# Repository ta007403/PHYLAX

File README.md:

# PHYLAX — Open-Source Bitcoin Hardware Wallet

**PHX-001 · Version 3 · Square Button**

PHYLAX (Greek *φύλαξ*, "guardian") is an open-source, Bitcoin-only hardware wallet built around a simple idea: no black-box chips, no wireless radios, no telemetry, and firmware you can read and verify yourself. This repository contains the KiCad hardware design files for the PHYLAX Version 3 board (square button variant).

🌐 Website: [phylaxwallet.com](https://phylaxwallet.com/)

> **Status:** In development — prototype targeted for Q4 2026. Hardware and firmware are subject to change.

---

## Why PHYLAX

- **Zero black-box chips** — no proprietary secure element; every component is one you can trace and verify.
- **Fully open firmware** — released under GPL v3.
- **Bitcoin-only** — no altcoins, no unnecessary attack surface.
- **No wireless radios, no telemetry** — the device only talks over USB-C, and only when you plug it in.
- **Built by the community** — the project is developed and audited in the open.

## What's in This Repository

This is a **KiCad 8 project** containing the schematic, PCB layout, 3D models, fabrication outputs, and supporting library parts for the PHYLAX board.

```
Phylax_Version_3 Square Button/
├── Phylax_Version_3.kicad_pro       # KiCad project file
├── Phylax_Version_3.kicad_sch       # Schematic
├── Phylax_Version_3.kicad_pcb       # PCB layout
├── 3D/                              # 3D models & case designs (.step, .stl, .FCStd, .scad)
├── Library/                         # Custom symbol, footprint, and 3D model libraries per part
├── Gerber/                          # Fabrication (Gerber/drill) outputs
├── PCB Outline/                     # Board outline drawings (DXF/PDF)
├── production/                      # BOM, position files, netlist, and production archives
├── Phylax_Version_3-backups/        # KiCad autosave/backup archives
├── fp-lib-table / sym-lib-table     # KiCad footprint & symbol library tables
└── Button Note.txt                  # Working design notes on component substitutions
```

### Key components

| Part | Role |
|---|---|
| STM32F205RET6 | Main microcontroller |
| SX1308 | Boost converter |
| MCP1703AT-3302E | 3.3V LDO regulator |
| USB4215-03-A | USB-C connector |
| SKHCBEA010 | Tactile push button |
| ABMM2-8.000MHZ-E2-T | Crystal oscillator |

*(See `production/bom.csv` for the full bill of materials.)*

## Getting Started

### Prerequisites

- [KiCad 8](https://www.kicad.org/download/) or later
- (Optional) [FreeCAD](https://www.freecad.org/) to view/edit the `.FCStd` case files
- (Optional) [OpenSCAD](https://openscad.org/) to view/edit the `.scad` case files

### Opening the project

1. Clone this repository:
   ```bash
   git clone https://github.com/ta007403/PHYLAX.git
   cd PHYLAX
   ```
2. Open `Phylax_Version_3.kicad_pro` in KiCad.
3. Schematic, PCB, and 3D viewer are all accessible from the KiCad project manager.

### Manufacturing

Fabrication-ready outputs (Gerbers, drill files, BOM, and pick-and-place data) are provided in the `Gerber/` and `production/` folders for sending directly to a PCB manufacturer/assembler.

## Contributing

PHYLAX is built in the open and welcomes community review and contributions — from schematic review to case design. Please open an issue or pull request with proposed changes. If you spot a design or safety issue, responsible disclosure is appreciated.

## License

Firmware and hardware design files are released under **GPL v3** unless otherwise noted. See the [PHYLAX manifesto](https://phylaxwallet.com/manifesto) and [specs](https://phylaxwallet.com/specs) for more on the project's philosophy and technical details.

## Links

- Website: [phylaxwallet.com](https://phylaxwallet.com/)
- Specifications: [phylaxwallet.com/specs](https://phylaxwallet.com/specs)
- Manifesto: [phylaxwallet.com/manifesto](https://phylaxwallet.com/manifesto)
- Journal / build updates: [phylaxwallet.com/journal](https://phylaxwallet.com/journal/)
- Facebook: [facebook.com/phylaxwallet](https://www.facebook.com/phylaxwallet)

---

*Not your keys, not your coins — PHYLAX gives you the keys.*

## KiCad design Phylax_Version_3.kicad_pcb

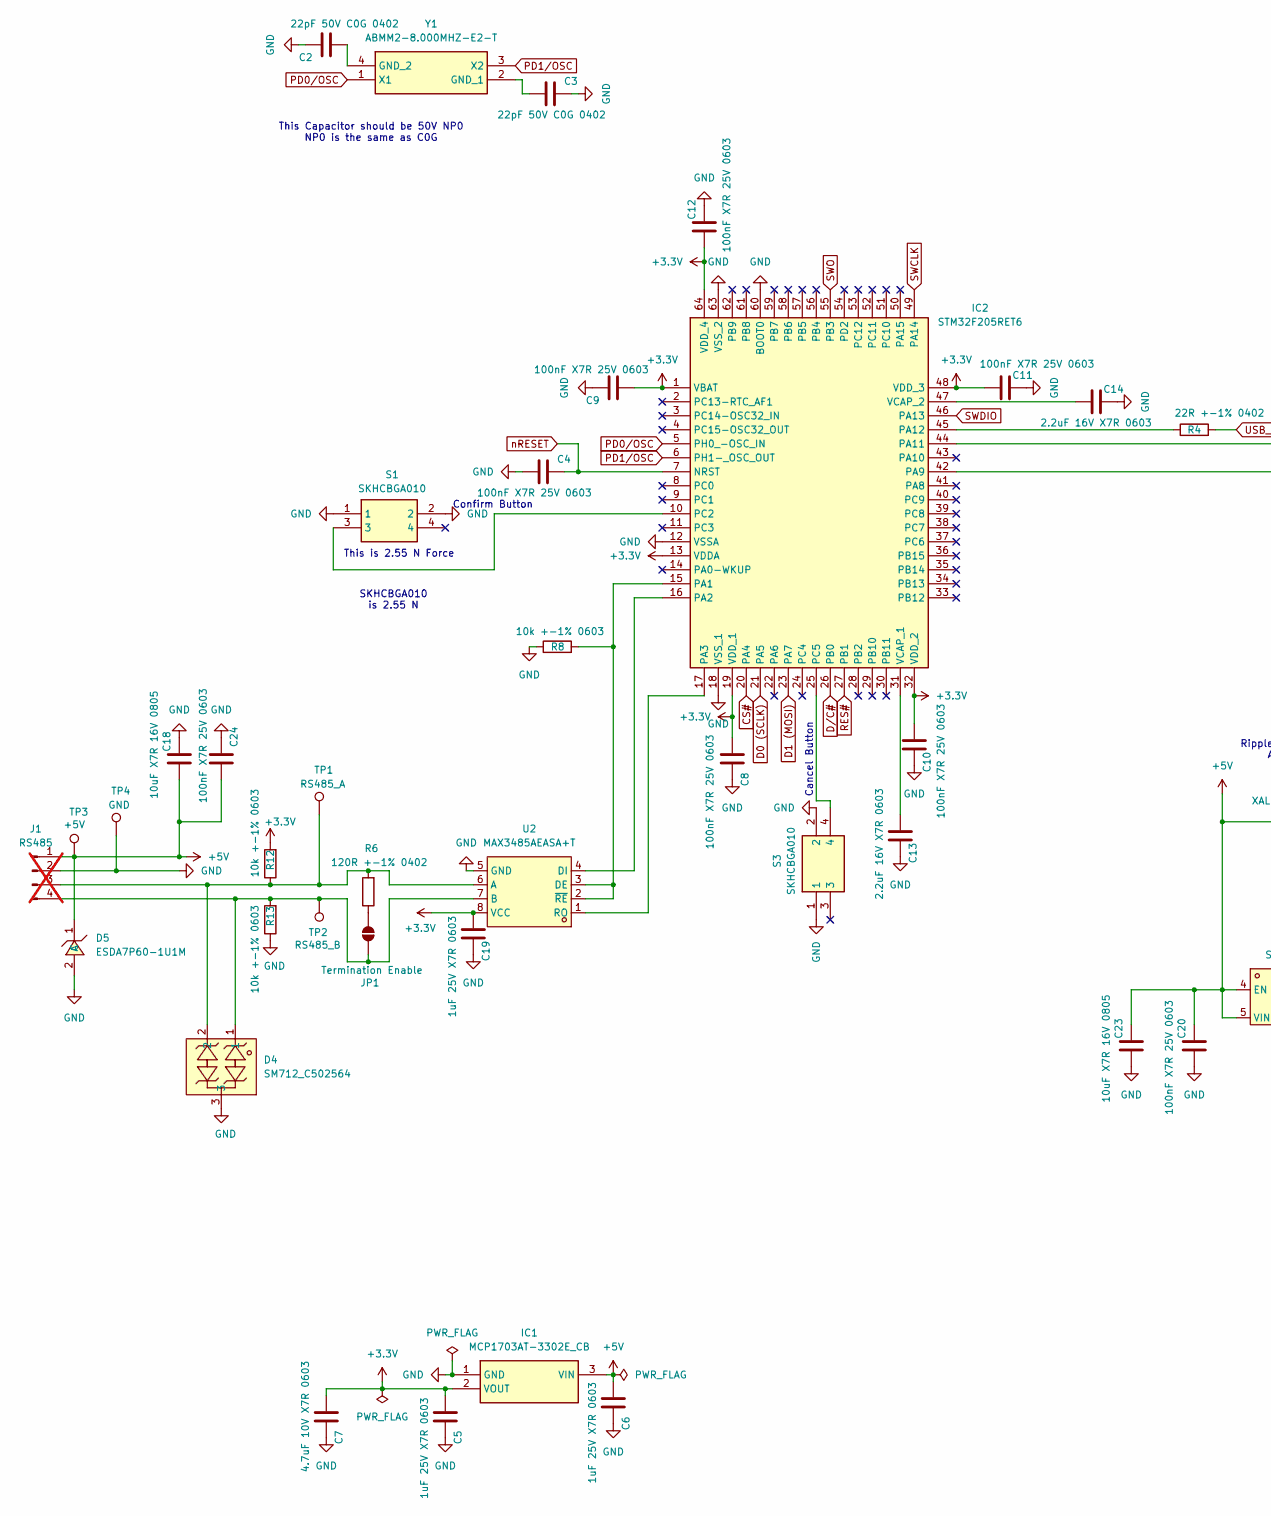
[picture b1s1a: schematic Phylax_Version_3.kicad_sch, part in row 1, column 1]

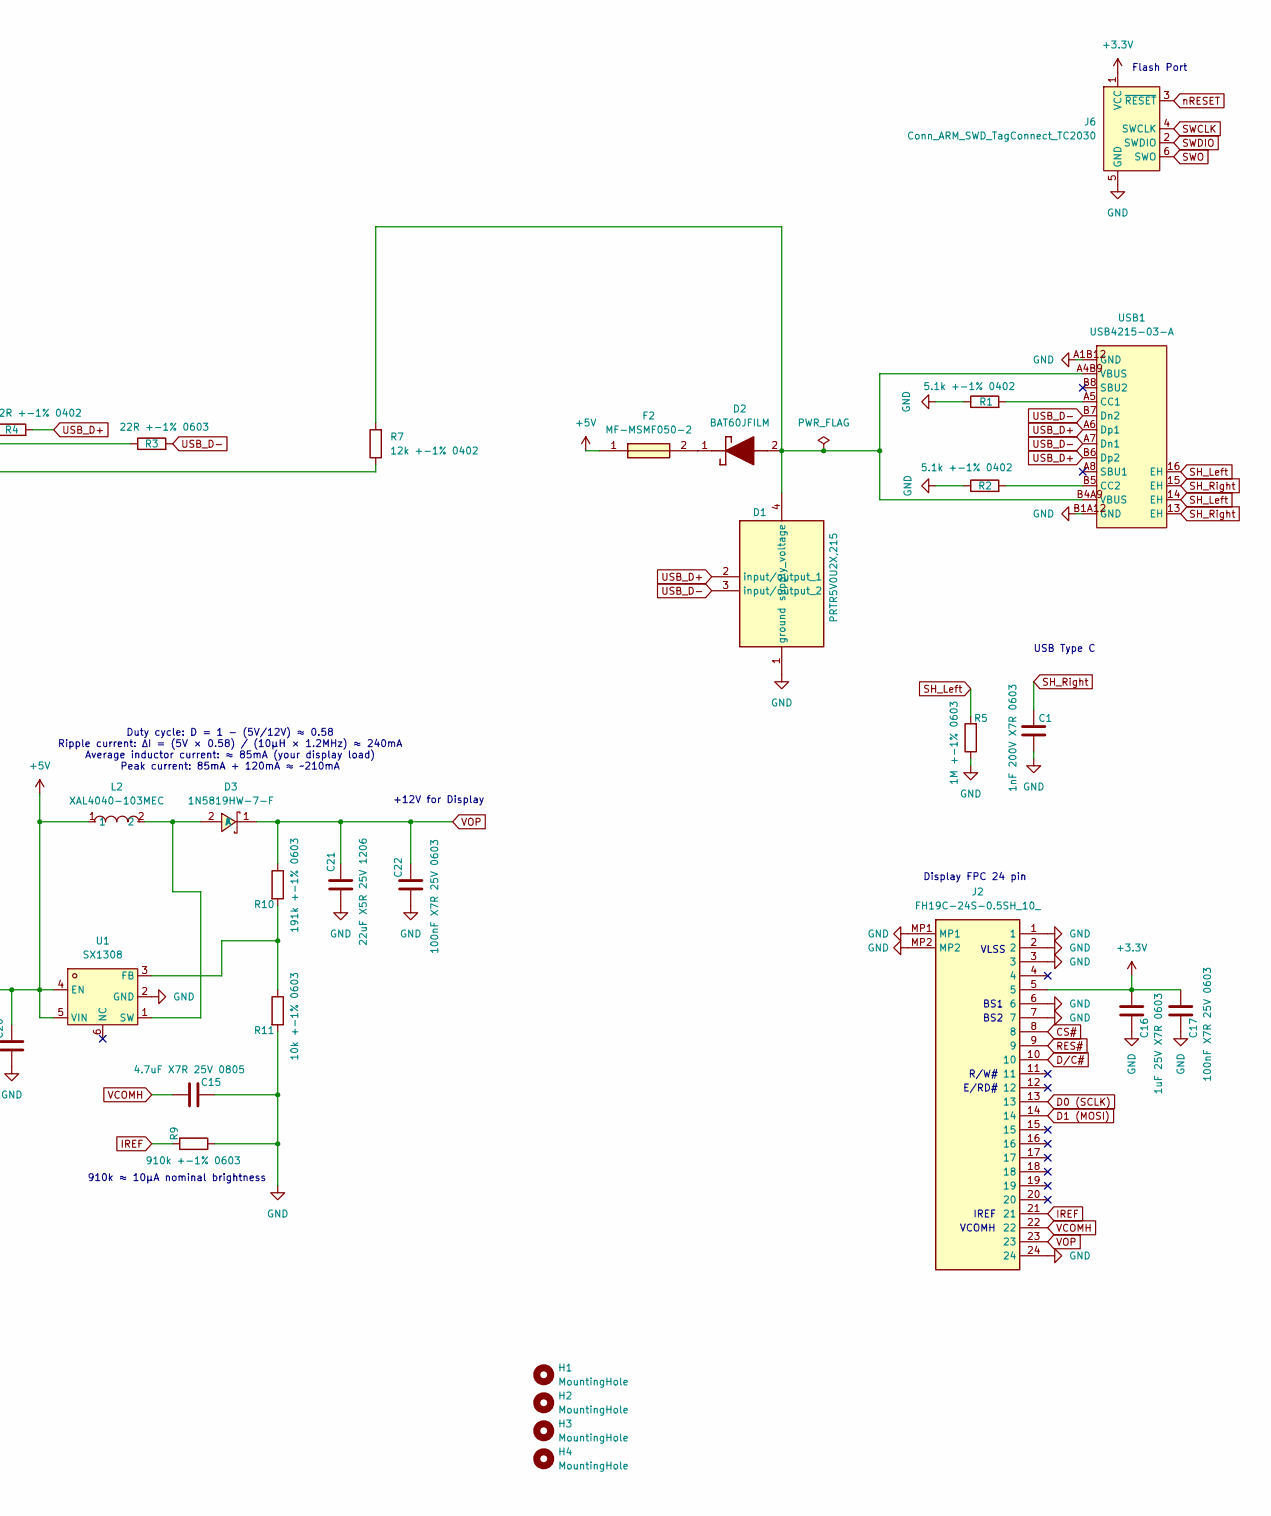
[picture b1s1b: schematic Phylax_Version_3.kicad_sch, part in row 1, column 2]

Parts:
C1: 1nF 200V X7R 0603; C_0603_1608Metric_Pad1.08x0.95mm_HandSolder; LCSC Part # C282243
C2, C3: 22pF 50V C0G 0402; C_0402_1005Metric_Pad0.74x0.62mm_HandSolder; LCSC Part # C106203
C4, C8, C9, C10, C11, C12, C17, C20, C22, C24: 100nF X7R 25V 0603; C_0603_1608Metric_Pad1.08x0.95mm_HandSolder; LCSC Part # C14663
C5, C6, C16, C19: 1uF 25V X7R 0603; C_0603_1608Metric_Pad1.08x0.95mm_HandSolder; LCSC Part # C106858
C7: 4.7uF 10V X7R 0603; C_0603_1608Metric_Pad1.08x0.95mm_HandSolder; LCSC Part # C18185770
C13, C14: 2.2uF 16V X7R 0603; C_0603_1608Metric_Pad1.08x0.95mm_HandSolder; LCSC Part # C914769
C15: 4.7uF X7R 25V 0805; C_0805_2012Metric_Pad1.18x1.45mm_HandSolder; LCSC Part # C354262
C18, C23: 10uF X7R 16V 0805; C_0805_2012Metric_Pad1.18x1.45mm_HandSolder; LCSC Part # C326595
C21: 22uF X5R 25V 1206; C_1206_3216Metric_Pad1.33x1.80mm_HandSolder; LCSC Part # C2178233
D1: PRTR5V0U2X,215; PRTR5V0U2X; Mouser Part Number 771-PRTR5V0U2X-T/R
D2: BAT60JFILM; SOD2513X117N; Mouser Part Number 511-BAT60JFILM
D3: 1N5819HW-7-F; SOD-123_L2.7-W1.6-LS3.7-RD; MPN 1N5819HW-7-F; LCSC Part C82544
D4: SM712_C502564; SOT-23-3_L2.9-W1.6-P1.90-LS2.8-BR; MPN SM712; LCSC Part C502564
D5: ESDA7P60-1U1M; D1610-RD; MPN ESDA7P60-1U1M; LCSC Part C1975146
F2: MF-MSMF050-2; FUSC4632X85N; Mouser Part Number 652-MF-MSMF050-2
H1, H2, H3, H4: MountingHole; MountingHole_3.2mm_M3
IC1: MCP1703AT-3302E_CB; SOT95P255X145-3N; Mouser Part Number 579-MCP1703AT3302ECB
IC2: STM32F205RET6; QFP50P1200X1200X160-64N; Mouser Part Number 511-STM32F205RET6
J1: RS485; PinHeader_1x04_P2.54mm_Vertical; not fitted
J2: FH19C-24S-0.5SH_10_; FH19C24S05SH10; Mouser Part Number 798-FH19C24S05SH10
J6: Conn_ARM_SWD_TagConnect_TC2030; Tag-Connect_TC2030-IDC-FP_2x03_P1.27mm_Vertical
JP1: Termination Enable; SolderJumper-2_P1.3mm_Open_RoundedPad1.0x1.5mm
L2: XAL4040-103MEC; IND-SMD_L4.0-W4.0_XAL4040; MPN XAL4040-103MEC; LCSC Part C5144883
R1, R2: 5.1k +-1% 0402; R_0402_1005Metric_Pad0.72x0.64mm_HandSolder; LCSC Part # C852856
R3: 22R +-1% 0603; R_0603_1608Metric_Pad0.98x0.95mm_HandSolder; LCSC Part # C313710
R4: 22R +-1% 0402; R_0402_1005Metric_Pad0.72x0.64mm_HandSolder; LCSC Part # C2686485
R5: 1M +-1% 0603; R_0603_1608Metric_Pad0.98x0.95mm_HandSolder; LCSC Part # C22356470
R6: 120R +-1% 0402; R_0603_1608Metric_Pad0.98x0.95mm_HandSolder; LCSC Part # C22787
R7: 12k +-1% 0402; R_0402_1005Metric_Pad0.72x0.64mm_HandSolder; LCSC Part # C2909316
R8, R11, R12, R13: 10k +-1% 0603; R_0603_1608Metric_Pad0.98x0.95mm_HandSolder; LCSC Part # C98220
R9: 910k +-1% 0603; R_0603_1608Metric_Pad0.98x0.95mm_HandSolder; LCSC Part # C23263
R10: 191k +-1% 0603; R_0603_1608Metric_Pad0.98x0.95mm_HandSolder; LCSC Part # C2974031
S1, S3: SKHCBGA010; Mouser Part Number 688-SKHCBGA010
TP1: RS485_A; TestPoint_Pad_1.0x1.0mm
TP2: RS485_B; TestPoint_Pad_1.0x1.0mm
TP3: +5V; TestPoint_Pad_1.0x1.0mm
TP4: GND; TestPoint_Pad_1.0x1.0mm
U1: SX1308; SOT-23-6_L2.9-W1.6-P0.95-LS2.8-BL; MPN SX1308; LCSC Part C78162
U2: MAX3485AEASA+T; SO-8_L4.9-W3.9-P1.27-LS5.9-BL; MPN MAX3485AEASA+T; LCSC Part C94609
USB1: USB4215-03-A; USB-C-SMD_GT-USB-7010B; MPN USB4215-03-A; LCSC Part C37616412
Y1: ABMM2-8.000MHZ-E2-T; ABMM2; Mouser Part Number 815-ABMM2-8-E2T

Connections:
+3.3V: C5.2, C7.2, C8.2, C9.2, C10.2, C11.2, C12.2, C16.2, C17.2, C19.2, IC1.2 (VOUT), IC2.1 (VBAT), IC2.13 (VDDA), IC2.19 (VDD_1), IC2.32 (VDD_2), IC2.48 (VDD_3), IC2.64 (VDD_4), J2.5, J6.1 (VCC), R12.2, U2.8 (VCC)
+5V: C6.2, C18.2, C20.1, C23.1, C24.1, D5.1 (C), F2.1, IC1.3 (VIN), J1.1, L2.1, TP3.1, U1.4 (EN), U1.5 (VIN)
CS#: IC2.20 (PA4), J2.8
D0 (SCLK): IC2.21 (PA5), J2.13
D1 (MOSI): IC2.23 (PA7), J2.14
D/C#: IC2.26 (PB0), J2.10
GND: C1.1, C2.1, C3.1, C4.2, C5.1, C6.1, C7.1, C8.1, C9.1, C10.1, C11.1, C12.1, C13.1, C14.1, C15.1, C16.1, C17.1, C18.1, C19.1, C20.2, C21.2, C22.2, C23.2, C24.2, D1.1 (ground), D4.3, D5.2 (A), IC1.1 (GND), IC2.12 (VSSA), IC2.18 (VSS_1), IC2.60 (BOOT0), IC2.63 (VSS_2), J1.2, J2.1, J2.2, J2.3, J2.6, J2.7, J2.24, J2.MP1, J2.MP2, J6.5 (GND), R1.1, R2.1, R5.1, R8.1, R9.1, R11.2, R13.1, S1.1, S1.2, S3.1, S3.2, TP4.1, U1.2 (GND), U2.5 (GND), USB1.A1B12 (GND), USB1.B1A12 (GND)
IREF: J2.21, R9.2
unnamed: D1.4 (supply_voltage), D2.2 (A), R7.2, USB1.A4B9 (VBUS), USB1.B4A9 (VBUS)
unnamed: D2.1 (K), F2.2
unnamed: D3.2 (A), L2.2, U1.1 (SW)
unnamed: IC2.15 (PA1), R8.2, U2.2 (~RE), U2.3 (DE)
unnamed: IC2.16 (PA2), U2.4 (DI)
unnamed: IC2.17 (PA3), U2.1 (RO)
unnamed: IC2.42 (PA9), R7.1
unnamed: IC2.44 (PA11), R3.1
unnamed: IC2.45 (PA12), R4.1
unnamed: IC2.10 (PC2), S1.3
unnamed: IC2.25 (PC5), S3.4
unnamed: C13.2, IC2.31 (VCAP_1)
unnamed: C14.2, IC2.47 (VCAP_2)
unnamed: D4.2, J1.3, R6.2, R12.1, TP1.1, U2.6 (A)
unnamed: D4.1, J1.4, JP1.1 (A), R13.2, TP2.1, U2.7 (B)
unnamed: JP1.2 (B), R6.1
unnamed: R10.2, R11.1, U1.3 (FB)
unnamed: R1.2, USB1.A5 (CC1)
unnamed: R2.2, USB1.B5 (CC2)
unnamed: C3.2, Y1.2 (GND_1)
unnamed: C2.2, Y1.4 (GND_2)
PD0/OSC: IC2.5 (PH0_-OSC_IN), Y1.1 (X1)
PD1/OSC: IC2.6 (PH1-_OSC_OUT), Y1.3 (X2)
RES#: IC2.27 (PB1), J2.9
SH_Left: R5.2, USB1.14 (EH), USB1.16 (EH)
SH_Right: C1.2, USB1.13 (EH), USB1.15 (EH)
SWCLK: IC2.49 (PA14), J6.4 (SWCLK)
SWDIO: IC2.46 (PA13), J6.2 (SWDIO)
SWO: IC2.55 (PB3), J6.6 (SWO)
USB_D+: D1.2 (input/output_1), R4.2, USB1.A6 (Dp1), USB1.B6 (Dp2)
USB_D-: D1.3 (input/output_2), R3.2, USB1.A7 (Dn1), USB1.B7 (Dn2)
VCOMH: C15.2, J2.22
VOP: C21.1, C22.1, D3.1 (K), J2.23, R10.1
nRESET: C4.1, IC2.7 (NRST), J6.3 (~RESET)

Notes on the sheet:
USB Type C
Display FPC 24 pin
910k ≈ 10µA nominal brightness
BS2
VCOMH
Flash Port
This is 2.55 N Force
R/W#
BS1
SKHCBGA010 is 2.55 N
Cancel Button
+12V for Display
VLSS
Confirm Button
Duty cycle: D = 1 − (5V/12V) ≈ 0.58 Ripple current: ΔI = (5V × 0.58) / (10µH × 1.2MHz) ≈ 240mA Average inductor current: ≈ 85mA (your display load) Peak current: 85mA + 120mA ≈ ~210mA
IREF
This Capacitor should be 50V NP0 NP0 is the same as C0G
E/RD#

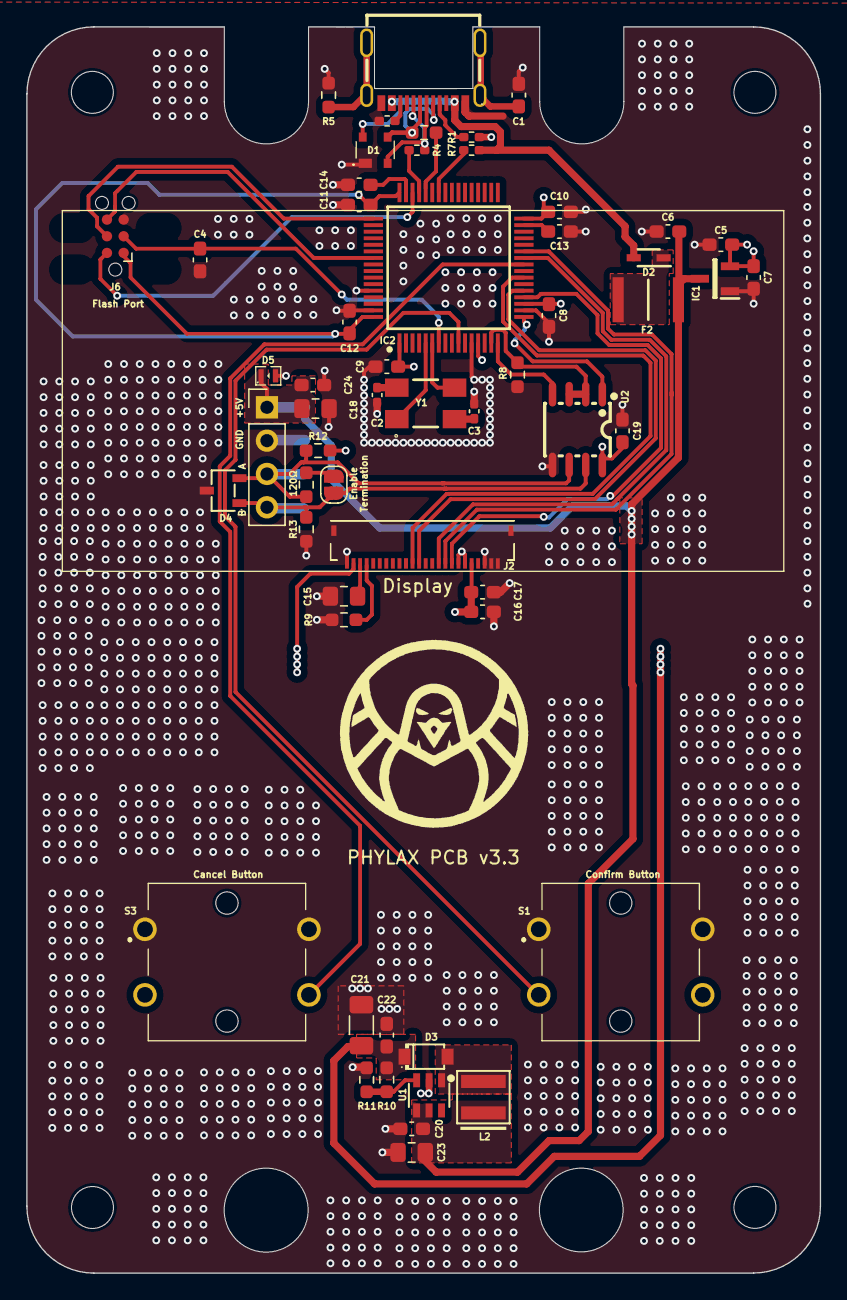
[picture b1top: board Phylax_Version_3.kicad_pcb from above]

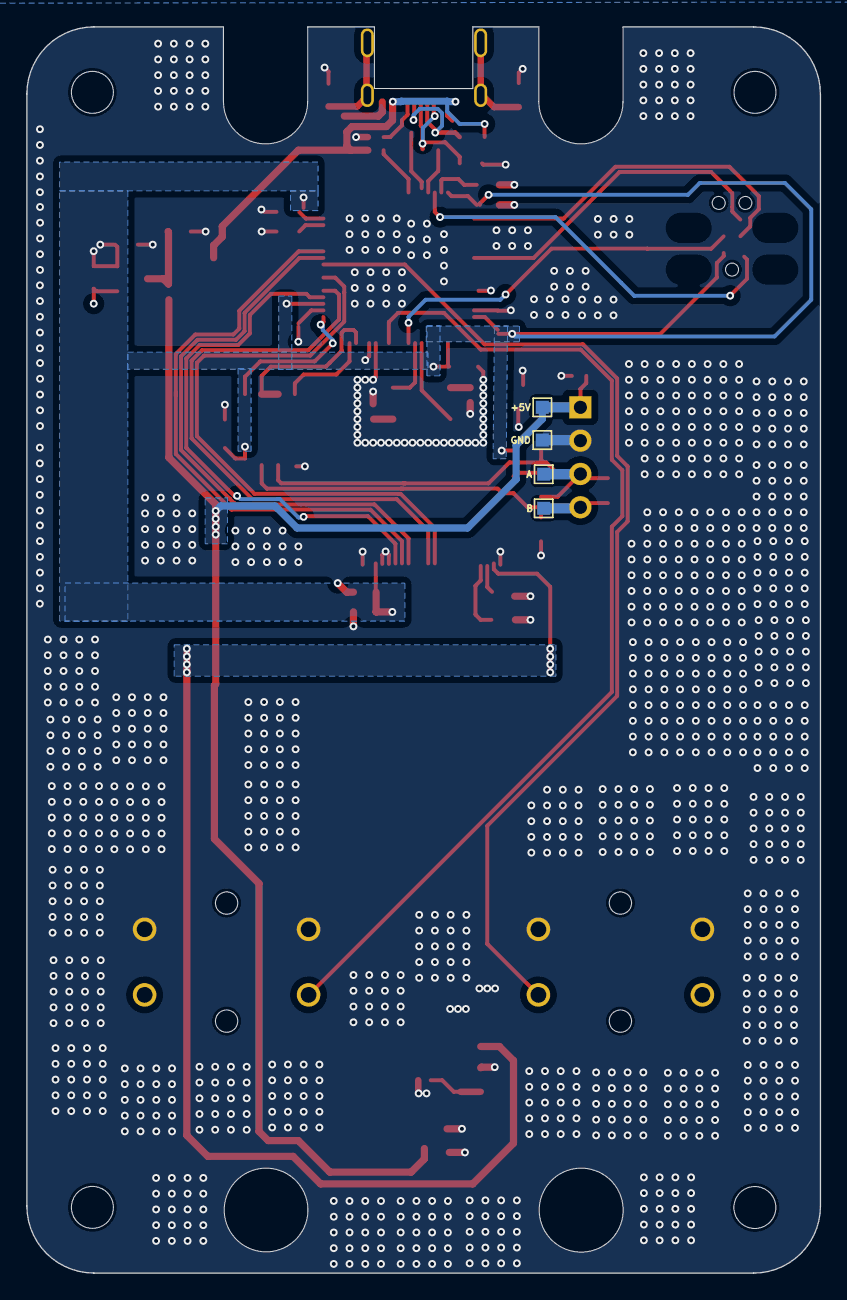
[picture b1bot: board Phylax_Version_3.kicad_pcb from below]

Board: 2 copper layers, 60.5 x 95.0 mm, 64 parts (4 on the bottom side), 42 nets.

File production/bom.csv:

Designator,Footprint,Quantity,Value,LCSC Part #
C1,0603,1,1nF 200V X7R 0603,C282243
"C10, C11, C12, C17, C20, C22, C24, C4, C8, C9",0603,10,100nF X7R 25V 0603,C14663
"C13, C14",0603,2,2.2uF 16V X7R 0603,C914769
C15,0805,1,4.7uF X7R 25V 0805,C354262
"C16, C19, C5, C6",0603,4,1uF 25V X7R 0603,C106858
"C18, C23",0805,2,10uF X7R 16V 0805,C326595
"C2, C3",0402,2,22pF 50V C0G 0402,C106203
C21,1206,1,22uF X5R 25V 1206,C2178233
C7,0603,1,4.7uF 10V X7R 0603,C18185770
D1,PRTR5V0U2X,1,"PRTR5V0U2X,215",C12333
D2,SOD2513X117N,1,BAT60JFILM,C133103
D3,SOD-123_L2.7-W1.6-LS3.7-RD,1,1N5819HW-7-F,C82544
D4,SOT-23-3_L2.9-W1.6-P1.90-LS2.8-BR,1,SM712_C502564,C502564
D5,D1610-RD,1,ESDA7P60-1U1M,C1975146
F2,FUSC4632X85N,1,MF-MSMF050-2,C17313
IC1,SOT95P255X145-3N,1,MCP1703AT-3302E_CB,C144183
IC2,QFP50P1200X1200X160-64N,1,STM32F205RET6,C66278
J1,PinHeader_1x04_P2.54mm_Vertical,1,RS485,
J2,FH19C24S05SH10,1,FH19C-24S-0.5SH_10_,C6555469
L2,IND-SMD_L4.0-W4.0_XAL4040,1,XAL4040-103MEC,C5144883
"R1, R2",0402,2,5.1k +-1% 0402,C852856
R10,0603,1,191k +-1% 0603,C2974031
"R11, R12, R13, R8",0603,4,10k +-1% 0603,C98220
R3,0603,1,22R +-1% 0603,C313710
R4,0402,1,22R +-1% 0402,C2686485
R5,0603,1,1M +-1% 0603,C22356470
R6,0603,1,120R +-1% 0402,C22787
R7,0402,1,12k +-1% 0402,C2909316
R9,0603,1,910k +-1% 0603,C23263
"S1, S3",SKHCBGA010,2,SKHCBGA010,C718965
TP1,TestPoint_Pad_1.0x1.0mm,1,RS485_A,
TP2,TestPoint_Pad_1.0x1.0mm,1,RS485_B,
TP3,TestPoint_Pad_1.0x1.0mm,1,+5V,
TP4,TestPoint_Pad_1.0x1.0mm,1,GND,
U1,SOT-23-6_L2.9-W1.6-P0.95-LS2.8-BL,1,SX1308,C78162
U2,SO-8_L4.9-W3.9-P1.27-LS5.9-BL,1,MAX3485AEASA+T,C94609
USB1,USB-C-SMD_GT-USB-7010B,1,USB4215-03-A,C37616412
Y1,ABMM2,1,ABMM2-8.000MHZ-E2-T,C431529
